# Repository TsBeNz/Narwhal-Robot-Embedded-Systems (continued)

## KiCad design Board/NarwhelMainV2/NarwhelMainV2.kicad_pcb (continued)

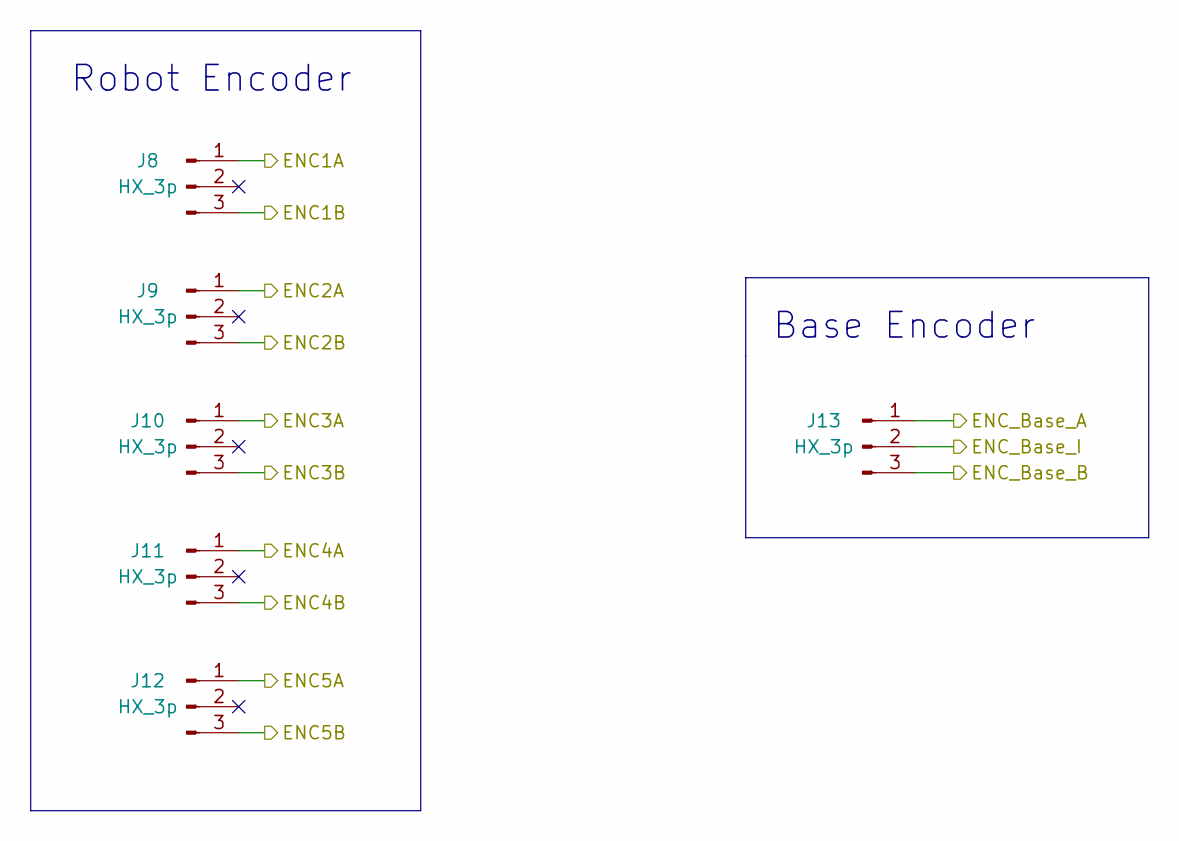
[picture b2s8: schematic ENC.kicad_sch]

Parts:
J8, J9, J10, J11, J12, J13: HX_3p; JST_XH_B3B-XH-A_1x03_P2.50mm_Vertical

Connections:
/Microcontroller/ENC_TImer1A: J11.1; also elsewhere on the board
/Microcontroller/ENC_TImer1B: J11.3; also elsewhere on the board
/Microcontroller/ENC_TImer2A: J13.1; also elsewhere on the board
/Microcontroller/ENC_TImer2B: J13.3; also elsewhere on the board
/Microcontroller/ENC_TImer2I: J13.2; also elsewhere on the board
/Microcontroller/ENC_TImer3A: J12.1; also elsewhere on the board
/Microcontroller/ENC_TImer3B: J12.3; also elsewhere on the board
/Microcontroller/ENC_TImer4A: J9.1; also elsewhere on the board
/Microcontroller/ENC_TImer4B: J9.3; also elsewhere on the board
/Microcontroller/ENC_TImer5A: J8.1; also elsewhere on the board
/Microcontroller/ENC_TImer5B: J8.3; also elsewhere on the board
/Microcontroller/ENC_TImer8A: J10.1; also elsewhere on the board
/Microcontroller/ENC_TImer8B: J10.3; also elsewhere on the board

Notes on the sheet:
Base Encoder
Robot Encoder

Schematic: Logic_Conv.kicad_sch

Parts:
C21, C22, C23, C24: 0.1uF; C_0603_1608Metric_Pad1.08x0.95mm_HandSolder
J4: Screw_Terminal_16p; TerminalBlock_Phoenix_PT-1,5-16-3.5-H_1x16_P3.50mm_Horizont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
U1, U2: TXS0108EPW; TSSOP-20_4.4x6.5mm_P0.65mm

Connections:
+3V3: C21.2, C23.2, U1.2 (VCCA), U2.2 (VCCA); also elsewhere on the board
+5V: C22.1, C24.1, U1.19 (VCCB), U2.19 (VCCB); also elsewhere on the board
/Microcontroller/DIR1: U1.5 (A4); also elsewhere on the board
/Microcontroller/DIR2: U1.4 (A3); also elsewhere on the board
/Microcontroller/DIR3: U1.3 (A2); also elsewhere on the board
/Microcontroller/DIR4: U1.1 (A1); also elsewhere on the board
/Microcontroller/DIR5: U2.9 (A8); also elsewhere on the board
/Microcontroller/EMSw0: U2.1 (A1); also elsewhere on the board
/Microcontroller/EN45: U1.9 (A8); also elsewhere on the board
/Microcontroller/EN123: U1.8 (A7); also elsewhere on the board
/Microcontroller/Griper0: U2.5 (A4); also elsewhere on the board
/Microcontroller/Logic Converter/5DIR1: J4.5, U1.16 (B4)
/Microcontroller/Logic Converter/5DIR2: J4.6, U1.17 (B3)
/Microcontroller/Logic Converter/5DIR3: J4.7, U1.18 (B2)
/Microcontroller/Logic Converter/5DIR4: J4.8, U1.20 (B1)
/Microcontroller/Logic Converter/5DIR5: J4.9, U2.12 (B8)
/Microcontroller/Logic Converter/5EMSw0: J4.16, U2.20 (B1)
/Microcontroller/Logic Converter/5EN45: J4.1, U1.12 (B8)
/Microcontroller/Logic Converter/5EN123: J4.2, U1.13 (B7)
/Microcontroller/Logic Converter/5Grpier0: J4.13, U2.16 (B4)
/Microcontroller/Logic Converter/5Grpier1: J4.14, U2.17 (B3)
/Microcontroller/Logic Converter/5Grpier2: J4.15, U2.18 (B2)
/Microcontroller/Logic Converter/5STEP1: J4.11, U2.14 (B6)
/Microcontroller/Logic Converter/5STEP2: J4.12, U2.15 (B5)
/Microcontroller/Logic Converter/5STEP3: J4.10, U2.13 (B7)
/Microcontroller/Logic Converter/5STEP4: J4.3, U1.14 (B6)
/Microcontroller/Logic Converter/5STEP5: J4.4, U1.15 (B5)
/Microcontroller/Logic Converter/Grpier1: U2.4 (A3); also elsewhere on the board
/Microcontroller/Logic Converter/Grpier2: U2.3 (A2); also elsewhere on the board
/Microcontroller/OE: U1.10 (OE), U2.10 (OE); also elsewhere on the board
/Microcontroller/STEP1: U2.7 (A6); also elsewhere on the board
/Microcontroller/STEP2: U2.6 (A5); also elsewhere on the board
/Microcontroller/STEP3: U2.8 (A7); also elsewhere on the board
/Microcontroller/STEP4: U1.7 (A6); also elsewhere on the board
/Microcontroller/STEP5: U1.6 (A5); also elsewhere on the board
GND: C21.1, C22.2, C23.1, C24.2, U1.11 (GND), U2.11 (GND); also elsewhere on the board

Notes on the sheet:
Logic Converter
Terminal

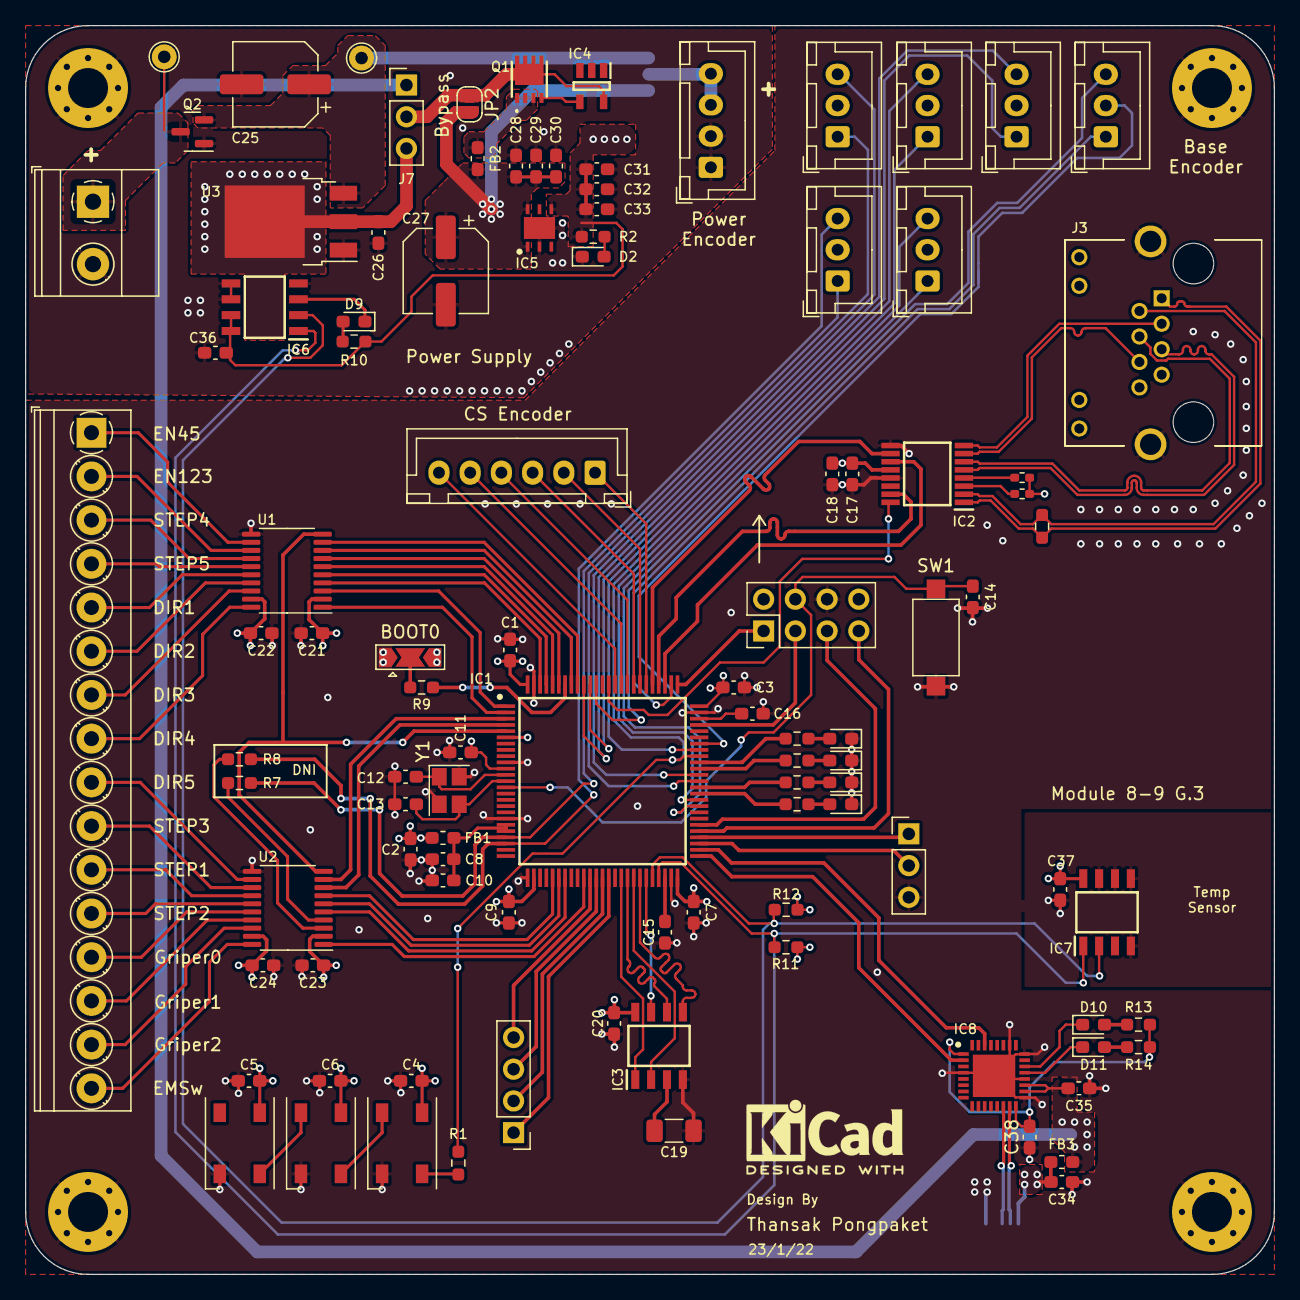
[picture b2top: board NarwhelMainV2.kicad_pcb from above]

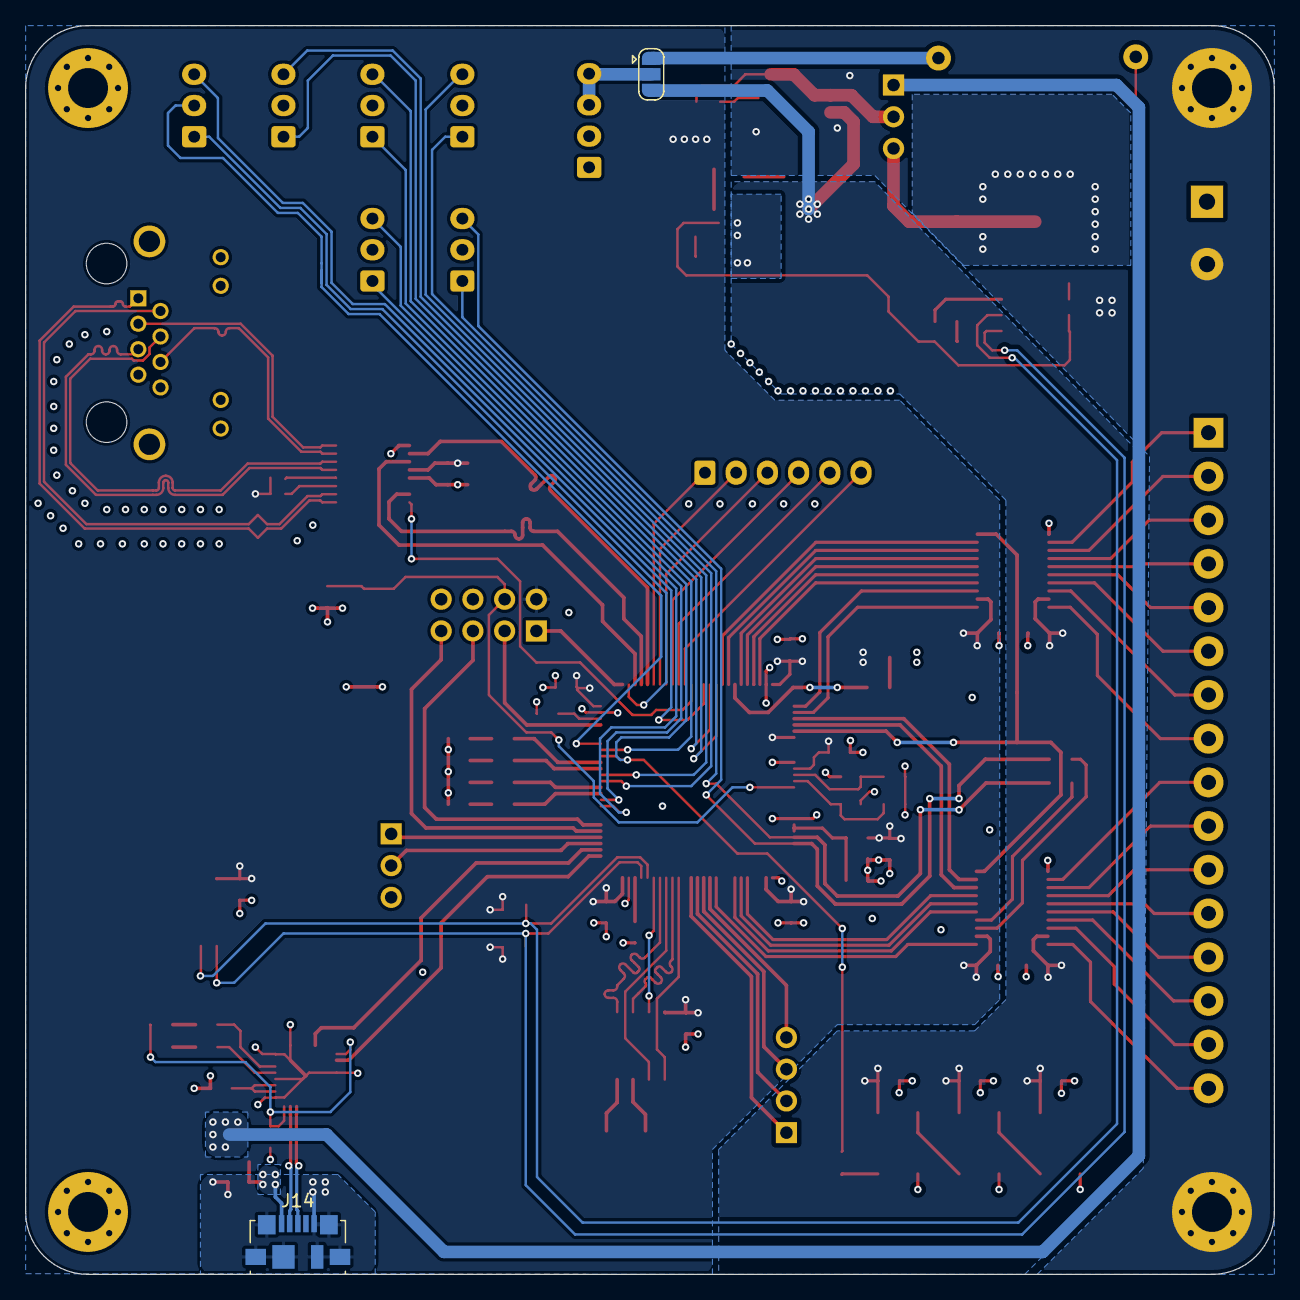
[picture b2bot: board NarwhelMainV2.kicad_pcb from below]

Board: 4 copper layers, 100.0 x 100.0 mm, 109 parts (2 on the bottom side), 125 nets.

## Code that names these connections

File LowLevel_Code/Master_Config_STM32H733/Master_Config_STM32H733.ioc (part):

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Mcu.Name=STM32H733VGTx
Mcu.Package=LQFP100
Mcu.UserName=STM32H733VGTx
PA0.Signal=S_TIM5_CH1
PA1.Signal=S_TIM5_CH2
PA10.GPIOParameters=GPIO_Label
PA10.GPIO_Label=ENC6I
PA10.Signal=GPIO_Input
PA11.Signal=USB_OTG_HS_DM
PA12.Signal=USB_OTG_HS_DP
PA13(JTMS/SWDIO).Mode=Serial_Wire
PA13(JTMS/SWDIO).Signal=DEBUG_JTMS-SWDIO
PA14(JTCK/SWCLK).Mode=Serial_Wire
PA14(JTCK/SWCLK).Signal=DEBUG_JTCK-SWCLK
PA15(JTDI).GPIOParameters=GPIO_Label
PA15(JTDI).GPIO_Label=ENC6A
PA15(JTDI).Signal=S_TIM2_CH1_ETR
PA6.GPIOParameters=GPIO_Label
PA6.GPIO_Label=STEP1
PA6.Signal=S_TIM13_CH1
PA7.GPIOParameters=GPIO_Label
PA7.GPIO_Label=STEP2
PA7.Signal=S_TIM14_CH1
PA8.GPIOParameters=GPIO_Label
PA8.GPIO_Label=ENC4A_Neopixel
PA8.Signal=S_TIM1_CH1
PA9.GPIOParameters=GPIO_Label
PA9.GPIO_Label=ENC4B
PA9.Signal=S_TIM1_CH2
PB1.GPIOParameters=GPIO_Label
PB1.GPIO_Label=EMSW0
PB1.Signal=GPXTI1
PB10.GPIOParameters=GPIO_Pu
PB10.GPIO_Pu=GPIO_PULLUP
PB10.Mode=I2C
PB10.Signal=I2C2_SCL
PB11.GPIOParameters=GPIO_Pu
PB11.GPIO_Pu=GPIO_PULLUP
PB11.Mode=I2C
PB11.Signal=I2C2_SDA
PB12.Mode=Asynchronous
PB12.Signal=UART5_RX
PB13.Mode=Asynchronous
PB13.Signal=UART5_TX
PB14.Mode=Asynchronous
PB14.Signal=USART1_TX
PB15.Mode=Asynchronous
PB15.Signal=USART1_RX
PB2.GPIOParameters=GPIO_Label
PB2.GPIO_Label=EMSW1
PB2.Signal=GPIO_Output
PB3(JTDO/TRACESWO).GPIOParameters=GPIO_Label
PB3(JTDO/TRACESWO).GPIO_Label=ENC6B
PB3(JTDO/TRACESWO).Signal=S_TIM2_CH2
PB4(NJTRST).GPIOParameters=GPIO_Label
PB4(NJTRST).GPIO_Label=ENC5A_GriperA
PB4(NJTRST).Signal=S_TIM3_CH1
PB5.GPIOParameters=GPIO_Label
PB5.GPIO_Label=ENC5B_GriperB
PB5.Signal=S_TIM3_CH2
PB6.GPIOParameters=GPIO_Label
PB6.GPIO_Label=EN45
PB6.Signal=GPIO_Output
PB7.GPIOParameters=GPIO_Label
PB7.GPIO_Label=EN123
PB7.Signal=GPIO_Output
PB8.GPIOParameters=GPIO_Label
PB8.GPIO_Label=STEP4
PB8.Signal=S_TIM16_CH1
PB9.GPIOParameters=GPIO_Label
PB9.GPIO_Label=STEP5
PB9.Signal=S_TIM17_CH1
PC10.Mode=Full_Duplex_Master
PC10.Signal=SPI3_SCK
PC11.Mode=Full_Duplex_Master
PC11.Signal=SPI3_MISO
PC12.Mode=Full_Duplex_Master
PC12.Signal=SPI3_MOSI
PC4.GPIOParameters=GPIO_Label
PC4.GPIO_Label=Griper0
PC4.Signal=GPIO_Output
PC5.Signal=ADCx_INP8
PC6.GPIOParameters=GPIO_Label
PC6.GPIO_Label=ENC3A
PC6.Signal=S_TIM8_CH1
PC7.GPIOParameters=GPIO_Label
PC7.GPIO_Label=ENC3B
PC7.Signal=S_TIM8_CH2
PC8.GPIOParameters=PinState,GPIO_Label
PC8.GPIO_Label=LED2
PC8.PinState=GPIO_PIN_RESET
PC8.Signal=GPIO_Output
PC9.GPIOParameters=PinState,GPIO_Label
PC9.GPIO_Label=LED1
PC9.PinState=GPIO_PIN_SET
PC9.Signal=GPIO_Output
PD0.GPIOParameters=PinState,GPIO_Label
PD0.GPIO_Label=SPI3_SS6
PD0.PinState=GPIO_PIN_SET
PD0.Signal=GPIO_Output
PD1.GPIOParameters=PinState,GPIO_Label
PD1.GPIO_Label=SPI3_SS5
PD1.PinState=GPIO_PIN_SET
PD1.Signal=GPIO_Output
PD12.GPIOParameters=GPIO_Label
PD12.GPIO_Label=ENC2A
PD12.Signal=S_TIM4_CH1
PD13.GPIOParameters=GPIO_Label
PD13.GPIO_Label=ENC2B
PD13.Signal=S_TIM4_CH2
PD14.GPIOParameters=GPIO_Label
PD14.GPIO_Label=LED4
PD14.Signal=GPIO_Output
PD15.GPIOParameters=GPIO_Label
PD15.GPIO_Label=LED3
PD15.Signal=GPIO_Output
PD2.GPIOParameters=PinState,GPIO_Label
PD2.GPIO_Label=SPI3_SS4
PD2.PinState=GPIO_PIN_SET
PD2.Signal=GPIO_Output
PD3.GPIOParameters=PinState,GPIO_Label
PD3.GPIO_Label=SPI3_SS3
PD3.PinState=GPIO_PIN_SET
PD3.Signal=GPIO_Output
PD4.GPIOParameters=PinState,GPIO_Label
PD4.GPIO_Label=SPI3_SS2
PD4.PinState=GPIO_PIN_SET
PD4.Signal=GPIO_Output
PD5.GPIOParameters=PinState,GPIO_Label
PD5.GPIO_Label=SPI3_SS1
PD5.PinState=GPIO_PIN_SET
PD5.Signal=GPIO_Output
PD6.GPIOParameters=GPIO_Label
PD6.GPIO_Label=SPI3_EN
PD6.Signal=GPIO_Output
PD8.Mode=Asynchronous
PD8.Signal=USART3_TX
PD9.Mode=Asynchronous
PD9.Signal=USART3_RX
PE0.GPIOParameters=GPIO_Label
PE0.GPIO_Label=DIR1
PE0.Signal=GPIO_Output
PE1.GPIOParameters=GPIO_Label
PE1.GPIO_Label=DIR2
PE1.Signal=GPIO_Output
PE11.GPIOParameters=GPIO_Label
PE11.GPIO_Label=EERAM_SS
PE11.Signal=GPIO_Output
PE12.GPIOParameters=GPIO_Label
PE12.GPIO_Label=SPI4_SCK
PE12.Mode=Full_Duplex_Master
PE12.Signal=SPI4_SCK
PE13.Mode=Full_Duplex_Master
PE13.Signal=SPI4_MISO
PE14.Mode=Full_Duplex_Master
PE14.Signal=SPI4_MOSI
PE15.GPIOParameters=GPIO_Label
PE15.GPIO_Label=EERAM_HOLD
PE15.Signal=GPIO_Output
PE2.GPIOParameters=GPIO_Label
PE2.GPIO_Label=DIR3
PE2.Signal=GPIO_Output
PE3.GPIOParameters=GPIO_Label
PE3.GPIO_Label=DIR4
PE3.Signal=GPIO_Output
PE4.GPIOParameters=GPIO_Label
PE4.GPIO_Label=DIR5
PE4.Signal=GPIO_Output
PE5.GPIOParameters=GPIO_ModeDefaultPP,GPIO_Speed,GPIO_PuPd
PE5.GPIO_ModeDefaultPP=GPIO_MODE_AF_PP
PE5.GPIO_PuPd=GPIO_NOPULL
PE5.GPIO_Speed=GPIO_SPEED_FREQ_LOW
PE5.Signal=S_TIM15_CH1
PE6.GPIOParameters=GPIO_Label
PE6.GPIO_Label=Output_EN
PE6.Signal=GPIO_Output
PE7.GPIOParameters=GPIO_Label
PE7.GPIO_Label=EMSW2
PE7.Signal=GPIO_Output
PE8.GPIOParameters=GPIO_Label
PE8.GPIO_Label=EMSW3
PE8.Signal=GPIO_Output
PE9.GPIOParameters=GPIO_Label
PE9.GPIO_Label=EMSW4
PE9.Signal=GPIO_Output
PH0-OSC_IN.Mode=HSE-External-Oscillator
PH0-OSC_IN.Signal=RCC_OSC_IN
PH1-OSC_OUT.Mode=HSE-External-Oscillator
PH1-OSC_OUT.Signal=RCC_OSC_OUT
RCC.SYSCLKFreq_VALUE=550000000
RCC.SYSCLKSource=RCC_SYSCLKSOURCE_PLLCLK
board=custom

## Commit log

2022-01-18 remember these files
2022-01-19 taskspace_traj
2022-01-19 taskspace_traj_lowlevel
2022-01-20 add new qv
2022-01-21 IVK_controlller test finish
2022-01-21 update IVK or something
2022-01-22 MCU Board Narwhals
2022-01-22 Update Project MCU Board
2022-01-23 Final Encoder PCB
2022-01-24 no longer define parameters
2022-01-24 Update Board
2022-01-26 update trajplot
2022-01-28 Update Code STM32 (Control ,Kalman & Trajectory Following)
2022-01-28 update lowlevel
2022-01-28 update control algorithm
2022-02-01 New IVK
    Matlab_simscape/Script/taskspace_traj
2022-02-02 update IPK False so sad
2022-02-02 testivk livescript
2022-02-05 Update Control
    - Control (Position Velocity)
    - Kalman filter (STM32,Matlab)
    - Encoder (AS5047U)
2022-02-06 Update Matlab Kalman filter
    - Kalman filter Function
    - Kalman filter Code gen
2022-02-09 update Kalman filter
2022-02-09 update iknarwhale5 ultimatecorrect
2022-02-09 update verified IPK
2022-02-09 update Code STM32
2022-02-11 update ultimatecorrectIVK
2022-02-12 change name Jv5 to Jv4 for understanding
2022-02-21 gen fpk
2022-02-22 update plot taskspace_traj
2022-02-24 Driver Step1
2022-02-25 Update Joint Trajectory
2022-02-27 update plot test taskspace traj
2022-03-16 Update Comu
2022-03-17 create file simscape for control
2022-04-12 update New PID Parameter
2022-04-13 Update Task Control
2022-04-17 update planning Traj.
2022-04-20 Update Control
2022-04-27 update low lv code
2022-04-27 Final Control 10.08PM
2022-04-27 Final Low LV with Chess Board Encoder
2022-05-13 Update Traj time
